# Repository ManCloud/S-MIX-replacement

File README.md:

# S-MIX-replacement

Replacement PCB for broken SNES S-MIX ICs and N64 AMP-NUS ICs

## Contributors
 * borti4938
   * he had the original idea of this board and helped a lot with the redesign.

## Changelog

v20210526
 * Moved to KiCad
 * changed overall layout
 * optimized to use single-layer
 
## Nice-to-know

During my investigations I found out, that the S-MIX of the SNES and the AMP-NUS of the N64 are functional identical.
I even swapped the chips between consoles and everything worked like a charm.

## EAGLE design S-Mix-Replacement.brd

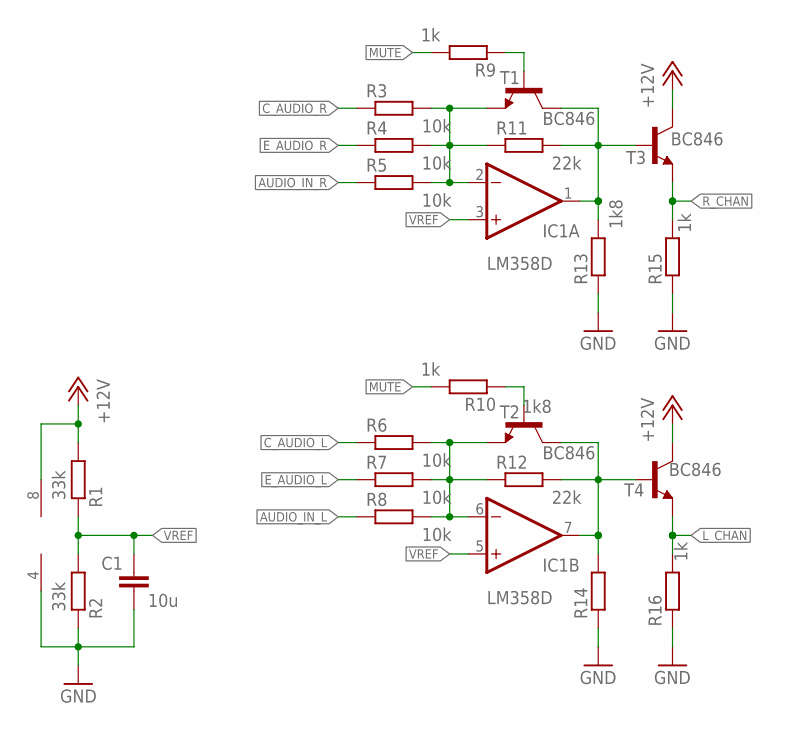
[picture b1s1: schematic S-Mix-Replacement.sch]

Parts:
C1: 10u; C1206
IC1: LM358D; SO08
R1, R2: 33k; R0805
R3, R4, R5, R6, R7, R8: 10k; R0805
R9, R10, R15, R16: 1k; R0805
R11, R12: 22k; R0805
R13, R14: 1k8; R0805
T1, T2, T3, T4: BC846; SOT23

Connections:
+12V: IC1.8 (V+), R1.2, T3.3 (C), T4.3 (C)
AUDIO_IN_L: R8.1
AUDIO_IN_R: R5.1
C_AUDIO_L: R6.1
C_AUDIO_R: R3.1
E_AUDIO_L: R7.1
E_AUDIO_R: R4.1
GND: C1.2, IC1.4 (V-), R2.2, R13.1, R14.1, R15.1, R16.1
L_CHAN: R16.2, T4.2 (E)
MUTE: R9.2, R10.2
unnamed: IC1.7 (OUT), R12.2, R14.2, T2.3 (C), T4.1 (B)
unnamed: IC1.2 (-IN), R3.2, R4.2, R5.2, R11.1, T1.2 (E)
unnamed: IC1.1 (OUT), R11.2, R13.2, T1.3 (C), T3.1 (B)
unnamed: R10.1, T2.1 (B)
unnamed: R9.1, T1.1 (B)
unnamed: IC1.6 (-IN), R6.2, R7.2, R8.2, R12.1, T2.2 (E)
R_CHAN: R15.2, T3.2 (E)
VREF: C1.1, IC1.3 (+IN), IC1.5 (+IN), R1.1, R2.1

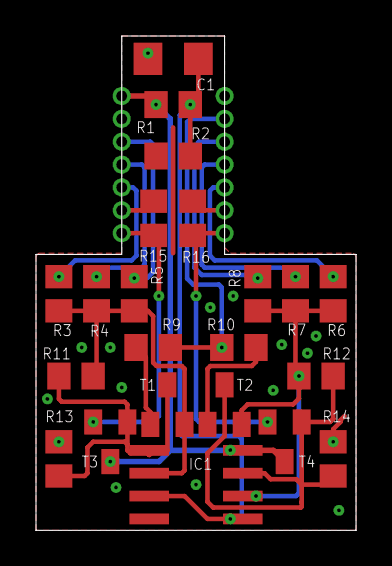
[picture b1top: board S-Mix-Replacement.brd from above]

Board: 2 copper layers, 17.8 x 27.5 mm, 22 parts (0 on the bottom side), 12 nets.

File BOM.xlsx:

Qty | Value | Alternative | Package | Parts | Description
6 | 10k | - | R0805 | R3, R4, R5, R6, R7, R8 | RESISTOR, European symbol
1 | 10u | - | C1206 | C1 | CAPACITOR, European symbol
4 | 1k | - | R0805 | R9, R10, R15, R16 | RESISTOR, European symbol
2 | 1k8 | - | R0805 | R13, R14 | RESISTOR, European symbol
2 | 22k | 24k | R0805 | R11, R12 | RESISTOR, European symbol
2 | 33k | - | R0805 | R1, R2 | RESISTOR, European symbol
4 | BC846 | 2SC2412K | SOT23 | T1, T2, T3, T4 | NPN TRANSISTOR
1 | LM358D | - | SO08 | IC1 | OP AMP also LM158; LM258; LM2904

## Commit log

2022-01-02 Updated repo to v20210526
